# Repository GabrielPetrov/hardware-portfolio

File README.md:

# PCB Design Portfolio

A collection of PCB projects I worked on while studying at TUES (ELSYS).

These were academic projects and were primarily intended as PCB design exercises rather than finished products. They cover work in KiCad and Cadence OrCAD, from simple analog boards to larger MCU-based designs.

## Projects

### Implant
Compact BLE sensor concept based around an nRF52811 and AD5941, with impedance and temperature sensing and energy-harvesting/power circuitry.

[Project files](./Implant/)

### DogTracker
Battery-powered ESP32-C3 tracker with GNSS, microSD storage, temperature measurement and associated power-management circuitry.

[Project files](./DogTracker/)

### DS0201v1.1
My first PCB design project. I produced 2-layer and 4-layer versions in Cadence OrCAD and later remade both versions in KiCad.

[Project files](./DS0201v1.1/)

### Analog Front End
Small thermistor measurement board using op-amp signal conditioning and an external ADC.

[Project files](./AFE/)

## Other projects

Two other embedded projects I've worked on are available separately:

- **[SeeIT](https://github.com/GabrielPetrov/SeeIT)** - ESP32 and Raspberry Pi-based computer-vision project.
- **[Furchikopter](https://github.com/Nikieprogramach/Furchikopter)** - remote-controlled aircraft using Arduino Uno boards and LoRa communication.

## Tools

Most of my PCB work has been done in KiCad. I originally learned the PCB design workflow using Cadence OrCAD 10.5 (Capture CIS, Layout and PSpice A/D), and I also have experience using LTspice for circuit simulation.

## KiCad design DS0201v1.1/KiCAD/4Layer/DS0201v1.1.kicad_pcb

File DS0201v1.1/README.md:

# DS0201

DS0201 was my first PCB design project and the board I originally used to learn the PCB design workflow.

The original versions were made in Cadence OrCAD 10.5. I produced both a 2-layer and a 4-layer layout, working from the same schematic.

The board is based around an STM32F103 and includes several peripheral and analog sections, including SD card storage, USB and battery circuitry, RS-232, switching/multiplexing and analog signal-conditioning circuitry.

## Original OrCAD versions

### Schematic

[View full schematic PDF](./Cadence%20OrCAD%20v10.5/Schematic_CaptureCIS/DS0201_schematic.pdf)

### 2-layer layout

### 4-layer layout

## KiCad versions

After completing the original OrCAD layouts, I recreated the board in KiCad in both 2-layer and 4-layer form.

The KiCad versions were done fairly quickly as an exercise in transferring the same design to a different EDA rather than as a complete layout redesign. Because of that, component placement and layout optimisation were not the main focus of those versions.

The project was useful for comparing the workflow of the two EDA packages and for seeing how the same design changes when moving between two and four copper layers.

### Schematic

[View full schematic PDF](./KiCAD/Schematic.pdf)

### 2-layer layout

[View full 2-layer PCB PDF](./KiCAD/2Layer/2LayerPCB.pdf)

### 4-layer layout

[View full 4-layer PCB PDF](./KiCAD/4Layer/4LayerPCB.pdf)

## Project files

The repository also contains the original OrCAD project files and the KiCad project files for both layouts.

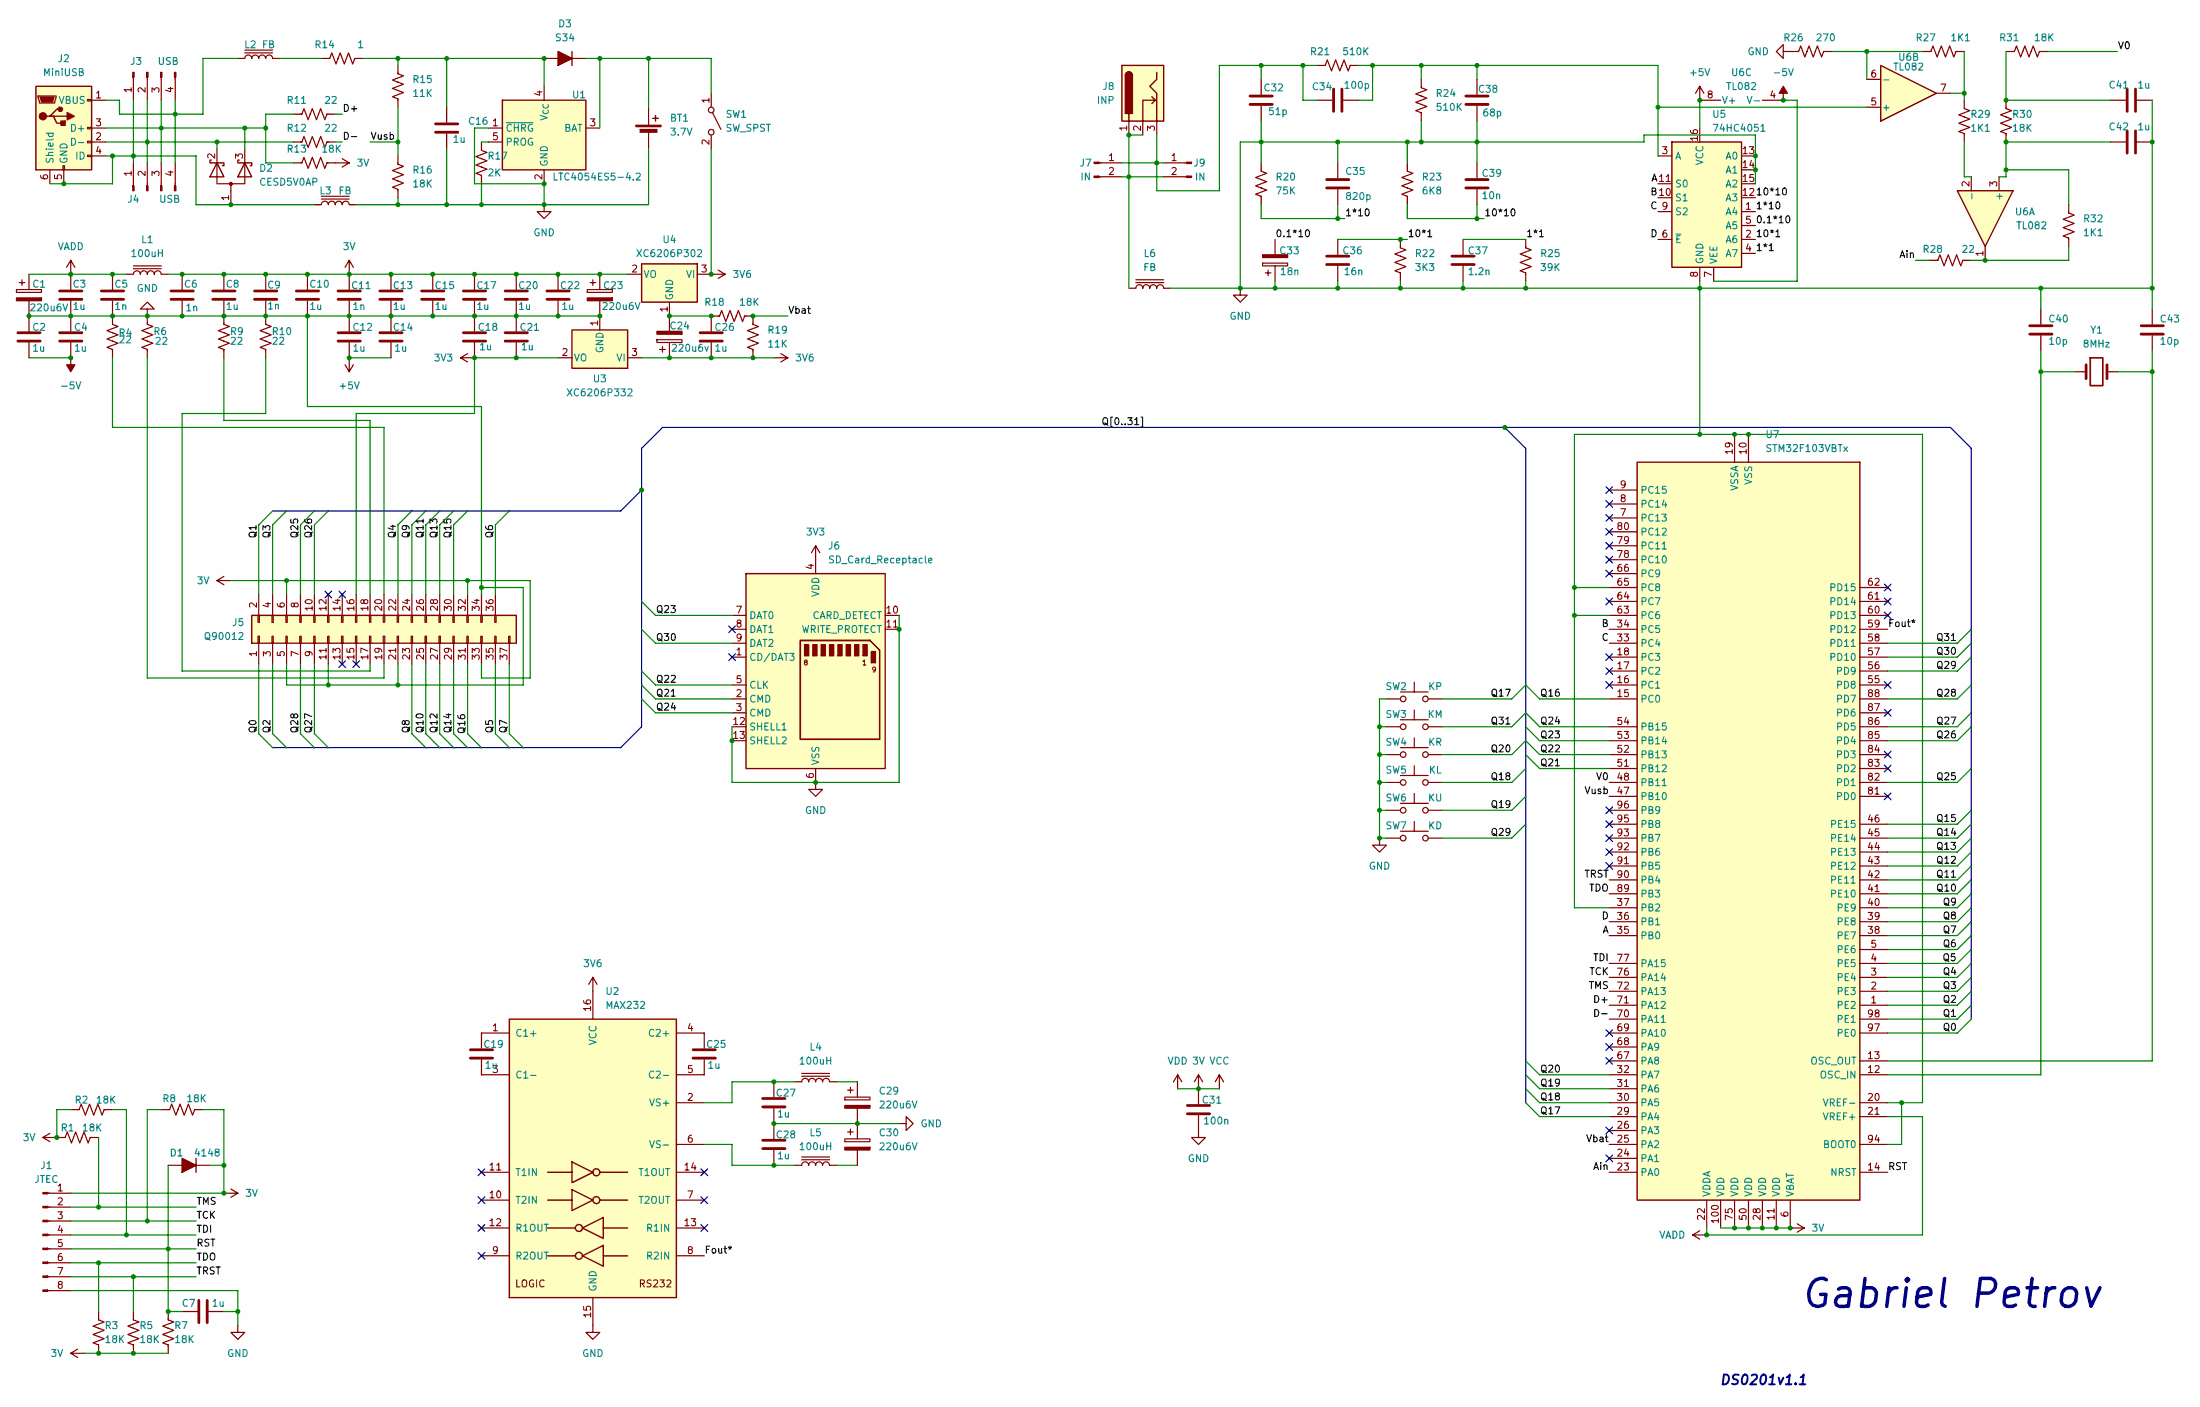
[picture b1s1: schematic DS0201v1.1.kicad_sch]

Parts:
BT1: 3.7V; JST_PH_B2B-PH-K_1x02_P2.00mm_Vertical
C1, C23, C29, C30: 220u6V; C_Radial_D6.3mm_H11.0mm_P2.50mm
C2, C3, C4, C7, C8, C10, C12, C13, C14, C15, C16, C17, C18, C19, C20, C21, C22, C25, C26, C27, C28, C41, C42: 1u; C_Disc_D3.8mm_W2.6mm_P2.50mm
C5, C6, C9, C11: 1n; C_Disc_D3.8mm_W2.6mm_P2.50mm
C24: 220u6v; C_Radial_D6.3mm_H11.0mm_P2.50mm
C31: 100n; C_Disc_D3.8mm_W2.6mm_P2.50mm
C32: 51p; C_Disc_D3.8mm_W2.6mm_P2.50mm
C33: 18n; C_Disc_D3.8mm_W2.6mm_P2.50mm
C34: 100p; C_Disc_D3.8mm_W2.6mm_P2.50mm
C35: 820p; C_Disc_D3.8mm_W2.6mm_P2.50mm
C36: 16n; C_Axial_L3.8mm_D2.6mm_P7.50mm_Horizontal
C37: 1.2n; C_Disc_D3.8mm_W2.6mm_P2.50mm
C38: 68p; C_Disc_D3.8mm_W2.6mm_P2.50mm
C39: 10n; C_Disc_D3.8mm_W2.6mm_P2.50mm
C40, C43: 10p; C_Disc_D3.8mm_W2.6mm_P2.50mm
D1: 4148; D_5W_P12.70mm_Horizontal
D2: CESD5V0AP; SOT-23
D3: S34; D_SOD-123F
J1: JTEC; Molex_Micro-Fit_3.0_43650-0815_1x08_P3.00mm_Vertical
J2: MiniUSB; USB_Micro-B_Wuerth_629105150521_CircularHoles
J3, J4: USB; Harwin_LTek-Male_04_P2.00mm_Vertical
J5: Q90012; Hirose_FH12-36S-0.5SH_1x36-1MP_P0.50mm_Horizontal
J6: SD_Card_Receptacle; CONN9_MSD-1_CUD
J7, J9: IN; Wuerth_WR-WTB_64800211622_1x02_P1.50mm_Vertical
J8: INP; MMCX_Molex_73415-0961_Horizontal_1.6mm-PCB
L1, L4, L5: 100uH; CP_Radial_D8.0mm_P3.50mm
L2, L3, L6: FB; CP_Radial_D8.0mm_P3.50mm
R1, R2, R3, R5, R7, R8, R13, R16, R18, R30, R31: 18K; R_Axial_DIN0204_L3.6mm_D1.6mm_P5.08mm_Horizontal
R4, R6, R9, R10, R11, R12, R28: 22; R_Axial_DIN0204_L3.6mm_D1.6mm_P5.08mm_Horizontal
R14: 1; R_Axial_DIN0204_L3.6mm_D1.6mm_P5.08mm_Horizontal
R15, R19: 11K; R_Axial_DIN0204_L3.6mm_D1.6mm_P5.08mm_Horizontal
R17: 2K; R_Axial_DIN0204_L3.6mm_D1.6mm_P5.08mm_Horizontal
R20: 75K; R_Axial_DIN0204_L3.6mm_D1.6mm_P5.08mm_Horizontal
R21, R24: 510K; R_Axial_DIN0204_L3.6mm_D1.6mm_P5.08mm_Horizontal
R22: 3K3; R_Axial_DIN0204_L3.6mm_D1.6mm_P5.08mm_Horizontal
R23: 6K8; R_Axial_DIN0204_L3.6mm_D1.6mm_P5.08mm_Horizontal
R25: 39K; R_Axial_DIN0204_L3.6mm_D1.6mm_P5.08mm_Horizontal
R26: 270; R_Axial_DIN0204_L3.6mm_D1.6mm_P5.08mm_Horizontal
R27, R29, R32: 1K1; R_Axial_DIN0204_L3.6mm_D1.6mm_P5.08mm_Horizontal
SW1: SW_SPST; SW_DIP_SPSTx01_Slide_9.78x4.72mm_W7.62mm_P2.54mm
SW2: KP; SW_PUSH_6mm
SW3: KM; SW_PUSH_6mm
SW4: KR; SW_PUSH_6mm
SW5: KL; SW_PUSH_6mm
SW6: KU; SW_PUSH_6mm
SW7: KD; SW_PUSH_6mm
U1: LTC4054ES5-4.2; TSOT-23-5
U2: MAX232; CERDIP-16_W7.62mm_SideBrazed
U3: XC6206P332; SOT-23-3
U4: XC6206P302; SOT-23-3
U5: 74HC4051; SOP-16_4.55x10.3mm_P1.27mm
U6: TL082; DIP-8_W7.62mm
U7: STM32F103VBTx; LQFP-100_14x14mm_P0.5mm
Y1: 8MHz; Crystal_AT310_D3.0mm_L10.0mm_Vertical

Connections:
3V: C6.1, C8.1, C9.1, C10.1, C11.1, C13.1, C15.1, C17.1, C20.1, C22.1, C23.1, C31.1, D1.1 (K), J1.1, J5.6, J5.32, J5.33, L1.2, R1.1, R2.1, R3.2, R5.2, R7.2, R8.2, R13.2, U4.2 (VO), U7.6 (VBAT), U7.11 (VDD), U7.28 (VDD), U7.50 (VDD), U7.75 (VDD), U7.100 (VDD)
3V3: C18.2, C21.2, J5.16, J6.4 (VDD), U3.2 (VO)
3V6: C24.1, C26.2, R19.2, SW1.2 (B), U2.16 (VCC), U3.3 (VI), U4.3 (VI)
+5V: C12.2, C14.2, U5.16 (VCC), U6.8 (V+)
-5V: C2.2, C4.2, U5.7 (VEE), U6.4 (V-)
/0.1*10: C33.2, U5.5 (A5)
/1*1: C37.1, R25.1, U5.4 (A7)
/1*10: C35.2, R20.2, U5.1 (A4)
/10*1: C36.1, R22.1, U5.2 (A6)
/10*10: C39.2, R23.2, U5.12 (A3)
/A: U5.11 (S0), U7.35 (PB0)
/Ain: R28.1, U7.23 (PA0)
/B: U5.10 (S1), U7.34 (PC5)
/C: U5.9 (S2), U7.33 (PC4)
/D: U5.6 (~E), U7.36 (PB1)
/D+: R11.2, U7.71 (PA12)
/D-: R12.2, U7.70 (PA11)
/Fout*: U2.8 (R2IN), U7.59 (PD12)
/Q0: J5.1, U7.97 (PE0)
/Q1: J5.2, U7.98 (PE1)
/Q2: J5.3, U7.1 (PE2)
/Q3: J5.4, U7.2 (PE3)
/Q4: J5.22, U7.3 (PE4)
/Q5: J5.35, U7.4 (PE5)
/Q6: J5.36, U7.5 (PE6)
/Q7: J5.37, U7.38 (PE7)
/Q8: J5.23, U7.39 (PE8)
/Q9: J5.24, U7.40 (PE9)
/Q10: J5.25, U7.41 (PE10)
/Q11: J5.26, U7.42 (PE11)
/Q12: J5.27, U7.43 (PE12)
/Q13: J5.28, U7.44 (PE13)
/Q14: J5.29, U7.45 (PE14)
/Q15: J5.30, U7.46 (PE15)
/Q16: J5.31, U7.15 (PC0)
/Q17: SW2.2, U7.29 (PA4)
/Q18: SW5.2, U7.30 (PA5)
/Q19: SW6.2, U7.31 (PA6)
/Q20: SW4.2, U7.32 (PA7)
/Q21: J6.2 (CMD), U7.51 (PB12)
/Q22: J6.5 (CLK), U7.52 (PB13)
/Q23: J6.7 (DAT0), U7.53 (PB14)
/Q24: J6.3 (CMD), U7.54 (PB15)
/Q25: J5.8, U7.82 (PD1)
/Q26: J5.10, U7.85 (PD4)
/Q27: J5.9, U7.86 (PD5)
/Q28: J5.7, U7.88 (PD7)
/Q29: SW7.2, U7.56 (PD9)
/Q30: J6.9 (DAT2), U7.57 (PD10)
/Q31: SW3.2, U7.58 (PD11)
/RST: C7.1, D1.2 (A), J1.5, R7.1, U7.14 (NRST)
/TCK: J1.3, R8.1, U7.76 (PA14)
/TDI: J1.4, R2.2, U7.77 (PA15)
/TDO: J1.6, R3.1, U7.89 (PB3)
/TMS: J1.2, R1.2, U7.72 (PA13)
/TRST: J1.7, R5.1, U7.90 (PB4)
/V0: R31.2, U7.48 (PB11)
/Vbat: R18.2, R19.1, U7.25 (PA2)
/Vusb: R15.2, R16.1, U7.47 (PB10)
GND: BT1.2 (-), C1.2, C2.1, C3.2, C4.1, C5.2, C6.2, C7.2, C8.2, C9.2, C10.2, C11.2, C12.1, C13.2, C14.1, C15.2, C16.2, C17.2, C18.1, C20.2, C21.1, C22.2, C23.2, C27.2, C28.1, C29.2, C30.1, C31.2, C32.1, C33.1, C35.1, C36.2, C37.2, C38.2, C39.1, C40.1, C41.2, C42.2, C43.1, J1.8, J5.5, J5.11, J5.21, J5.34, J6.6 (VSS), J6.10 (CARD_DETECT), J6.11 (WRITE_PROTECT), J6.12 (SHELL1), J6.13 (SHELL2), L3.2, L6.2, R4.1, R6.1, R9.1, R10.1, R16.2, R17.2, R20.1, R22.2, R23.1, R24.2, R25.2, R26.1, SW2.1, SW3.1, SW4.1, SW5.1, SW6.1, SW7.1, U1.1 (~CHRG), U1.2 (GND), U2.15 (GND), U3.1 (GND), U5.8 (GND), U5.13 (A0), U5.14 (A1), U5.15 (A2), U7.10 (VSS), U7.19 (VSSA), U7.20 (VREF-), U7.27 (VSS), U7.37 (PB2), U7.49 (VSS), U7.63 (PC6), U7.65 (PC8), U7.74 (VSS), U7.94 (BOOT0), U7.99 (VSS)
unnamed: BT1.1 (+), D3.1 (K), SW1.1 (A), U1.3 (BAT)
unnamed: C29.1, L4.2
unnamed: C30.2, L5.2
unnamed: C41.1, R30.1, R31.1
unnamed: D2.1 (A), J2.4 (ID), J2.5 (GND), J2.6 (Shield), J3.1, J4.1, L3.1
unnamed: C16.1, D3.2 (A), R14.2, R15.1, U1.4 (V_{CC})
unnamed: D2.3 (K), J2.3 (D+), J3.3, J4.3, R11.1, R13.1
unnamed: D2.2 (K), J2.2 (D-), J3.2, J4.2, R12.1
unnamed: J2.1 (VBUS), J3.4, J4.4, L2.1
unnamed: J5.17, R10.2
unnamed: J5.18, R9.2
unnamed: J5.19, R6.2
unnamed: J5.20, R4.2
unnamed: C32.2, C34.2, J7.1, J8.3, J9.1, R21.1
unnamed: J7.2, J8.1, J8.2, J9.2, L6.1
unnamed: L2.2, R14.1
unnamed: R27.2, R29.1, U6.7
unnamed: R28.2, R32.2, U6.1
unnamed: R17.1, U1.5 (PROG)
unnamed: C19.1, U2.1 (C1+)
unnamed: C19.2, U2.3 (C1-)
unnamed: C25.1, U2.4 (C2+)
unnamed: C25.2, U2.5 (C2-)
unnamed: C27.1, L4.1, U2.2 (VS+)
unnamed: C28.2, L5.1, U2.6 (VS-)
unnamed: C24.2, C26.1, R18.1, U4.1 (GND)
unnamed: C34.1, C38.1, R21.2, R24.1, U5.3 (A), U6.5 (+)
unnamed: C42.1, R30.2, R32.1, U6.3 (+)
unnamed: R29.2, U6.2 (-)
unnamed: R26.2, R27.1, U6.6 (-)
unnamed: C40.2, U7.12 (OSC_IN), Y1.1
unnamed: C43.2, U7.13 (OSC_OUT), Y1.2
VADD: C1.1, C3.1, C5.1, L1.1, U7.21 (VREF+), U7.22 (VDDA)

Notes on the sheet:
Gabriel Petrov
DS0201v1.1

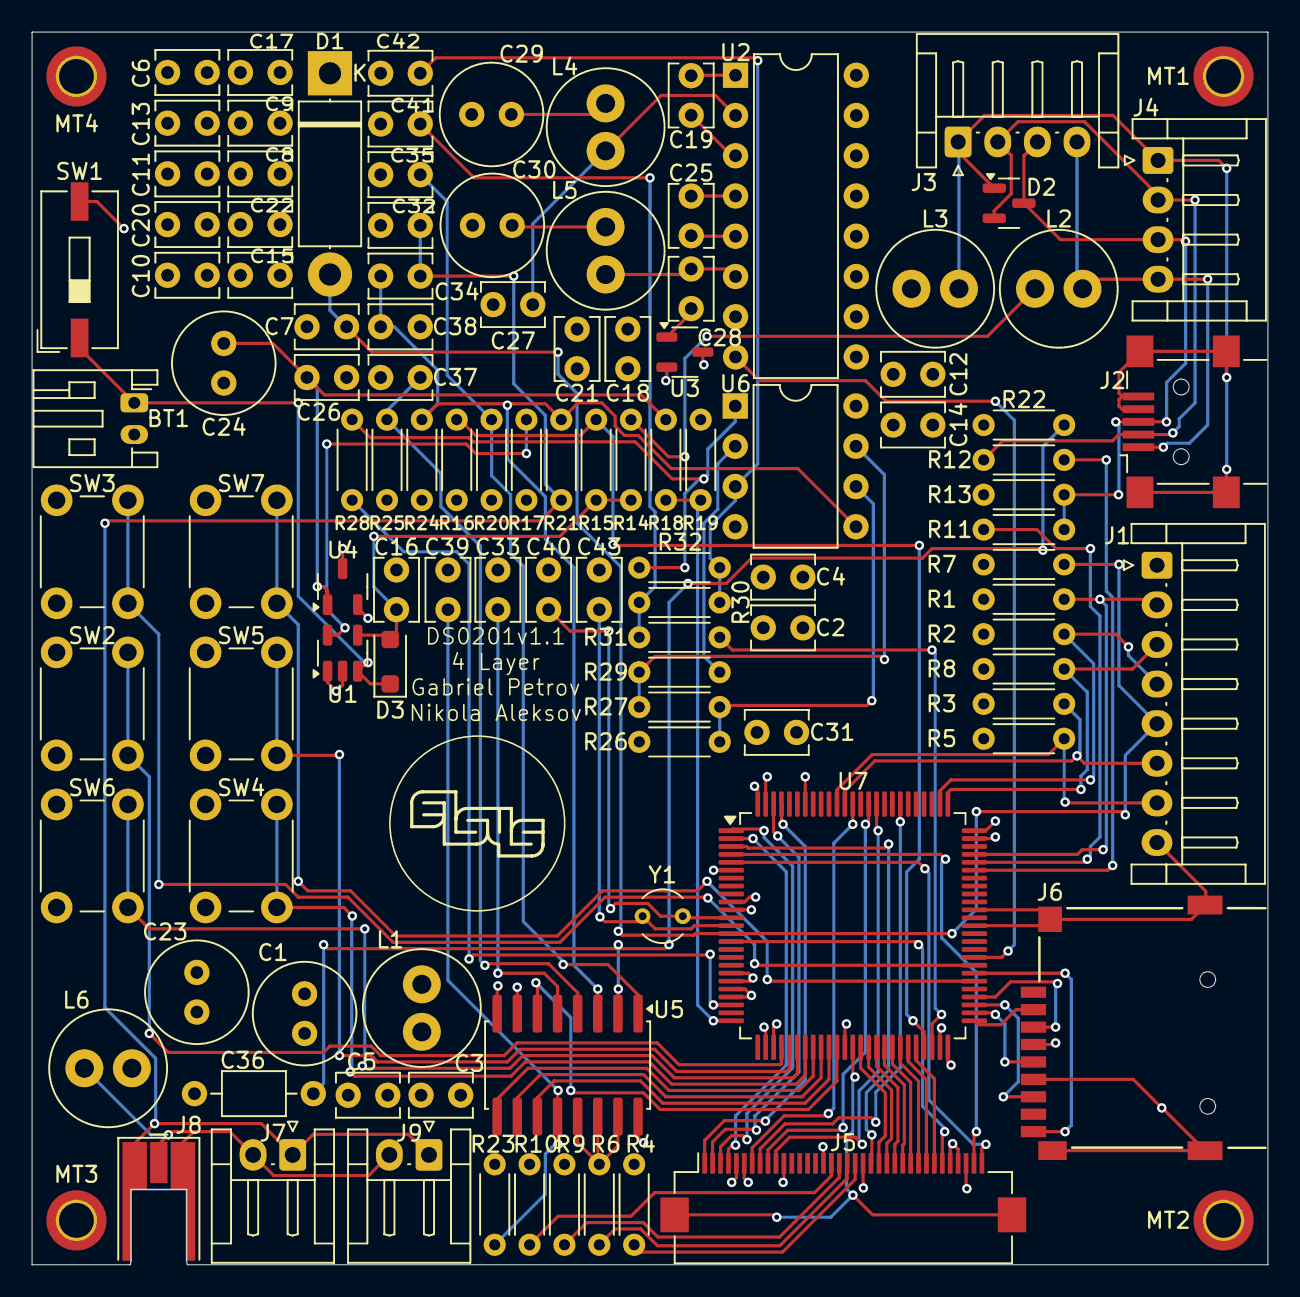
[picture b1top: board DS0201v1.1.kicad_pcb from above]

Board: 4 copper layers, 78.0 x 77.8 mm, 113 parts (0 on the bottom side), 93 nets.

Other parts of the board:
MT1, MT2, MT3, MT4: MountingHole_2.2mm_M2_DIN965_Pad_TopBottom

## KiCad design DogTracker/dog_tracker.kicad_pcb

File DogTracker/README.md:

# DogTracker

DogTracker was a school project for a small battery-powered tracking device.

The board is based around an ESP32-C3 and an L80-R GNSS module. It also includes microSD storage, temperature measurement, a serial EEPROM, and the supporting battery charging and power circuitry.

The schematic and PCB were designed in KiCad.

## Main parts

- ESP32-C3-WROOM-02
- L80-R GNSS module
- MicroSD card
- Li-ion battery and USB-C charging
- TPS63031 buck-boost converter
- Thermistor measurement circuitry
- External ADC
- Serial EEPROM

## Design

The board was designed to fit inside a roughly 50 mm circular outline. The project involved fitting the MCU, GNSS module, storage, sensors and power circuitry onto the same board while keeping the different sections reasonably separated.

## Schematic

[View full schematic PDF](./DogTrackSchema.pdf)

## PCB

[View full PCB PDF](./dog_tracker-User_2.pdf)

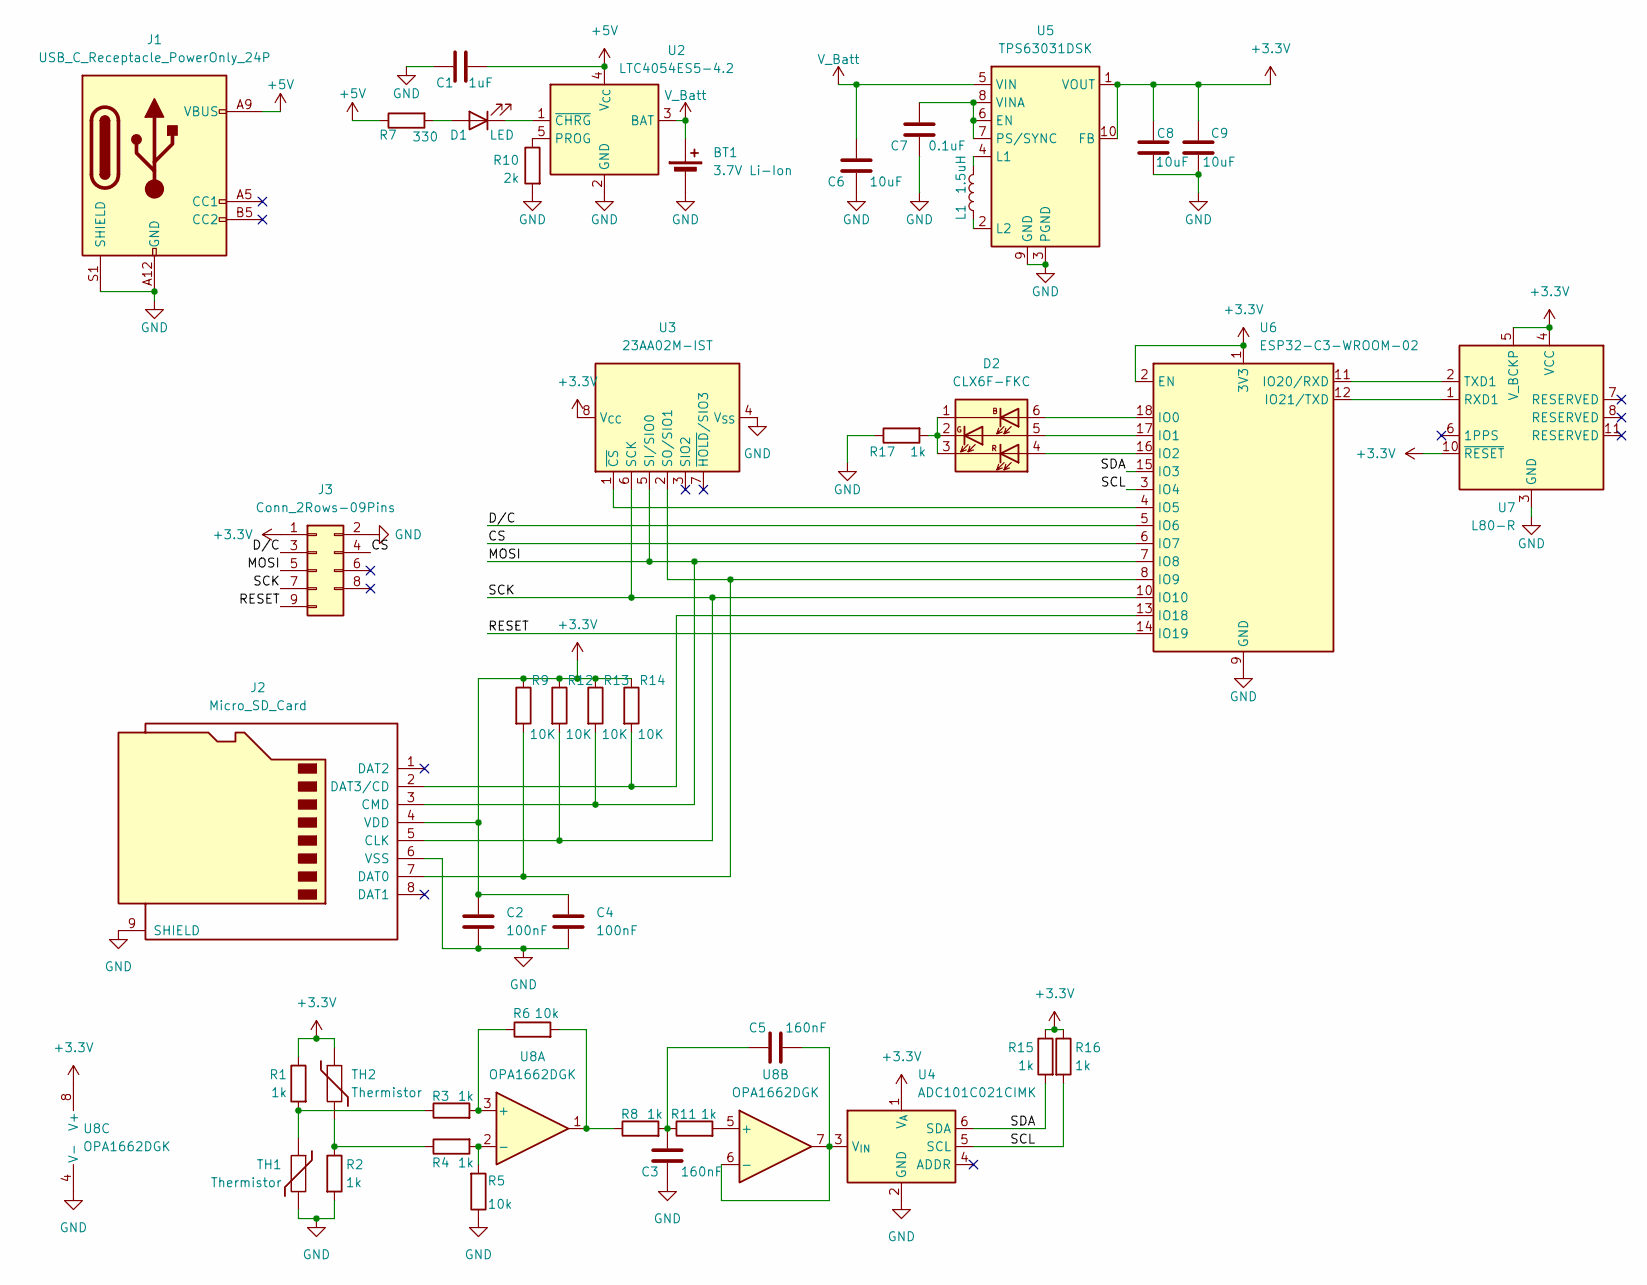
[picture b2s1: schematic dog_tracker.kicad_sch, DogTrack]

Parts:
BT1: 3.7V Li-Ion; vapcell_inr_26350_footprint
C1: 1uF; R_0201_0603Metric
C2, C4: 100nF; R_0201_0603Metric
C3, C5: 160nF; R_0201_0603Metric
C6, C8, C9: 10uF; C_0201_0603Metric
C7: 0.1uF; C_0201_0603Metric
D1: LED; D_0201_0603Metric
D2: CLX6F-FKC; LED_RGB_PLCC-6
J1: USB_C_Receptacle_PowerOnly_24P; USB_C_Receptacle_Amphenol_124019772112A
J2: Micro_SD_Card; microSD_HC_Hirose_DM3BT-DSF-PEJS
J3: Conn_2Rows-09Pins; Hirose_DF13C_CL535-0410-4-51_1x10-1MP_P1.25mm_Vertical
L1: 1.5uH; L_0201_0603Metric
R1, R2, R3, R4, R8, R11, R15, R16, R17: 1k; R_0201_0603Metric
R5, R6: 10k; R_0201_0603Metric
R7: 330; R_0201_0603Metric
R9, R12, R13, R14: 10K; R_0201_0603Metric
R10: 2k; R_0201_0603Metric
TH1, TH2: Thermistor; R_0201_0603Metric
U2: LTC4054ES5-4.2; TSOT-23-5
U3: 23AA02M-IST; TSSOP-8_4.4x3mm_P0.65mm
U4: ADC101C021CIMK; SOT-23-6
U5: TPS63031DSK; WSON-10-1EP_2.5x2.5mm_P0.5mm_EP1.2x2mm
U6: ESP32-C3-WROOM-02
U7: L80-R; Quectel_L80-R
U8: OPA1662DGK; VSSOP-8_3x3mm_P0.65mm

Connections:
+3.3V: C2.1, C4.1, C8.2, C9.2, J2.4 (VDD), J3.1, R1.1, R9.1, R12.1, R13.1, R14.1, R15.1, R16.1, TH2.1, U3.8 (V_{CC}), U4.1 (V_{A}), U5.1 (VOUT), U5.10 (FB), U6.1 (3V3), U6.2 (EN), U7.4 (VCC), U7.5 (V_BCKP), U7.10 (~RESET), U8.8 (V+)
+5V: C1.1, J1.A4 (VBUS), J1.A9 (VBUS), J1.B4 (VBUS), J1.B9 (VBUS), R7.1, U2.4 (V_{CC})
/CS: J3.4, U6.6 (IO7)
/D/C: J3.3, U6.5 (IO6)
/MOSI: J2.3 (CMD), J3.5, R13.2, U3.5 (SI/SIO0), U6.7 (IO8)
/RESET: J3.9, U6.14 (IO19)
/SCK: J2.5 (CLK), J3.7, R12.2, U3.6 (SCK), U6.10 (IO10)
/SCL: R16.2, U4.5 (SCL), U6.3 (IO4)
/SDA: R15.2, U4.6 (SDA), U6.15 (IO3)
GND: BT1.2 (-), C1.2, C2.2, C3.2, C4.2, C6.1, C7.1, C8.1, C9.1, J1.A1 (GND), J1.A12 (GND), J1.B1 (GND), J1.B12 (GND), J1.S1 (SHIELD), J2.6 (VSS), J2.9 (SHIELD), J3.2, R2.2, R5.1, R10.2, R17.1, TH1.2, U2.2 (GND), U3.4 (V_{SS}), U4.2 (GND), U5.3 (PGND), U5.9 (GND), U5.11 (PGND), U6.9 (GND), U6.19 (GND), U7.3 (GND), U7.12 (GND), U8.4 (V-)
unnamed: C3.1, C5.2, R8.2, R11.1
unnamed: D1.2 (A), R7.2
unnamed: D1.1 (K), U2.1 (~CHRG)
unnamed: D2.6 (AB), U6.18 (IO0)
unnamed: D2.5 (AG), U6.17 (IO1)
unnamed: D2.4 (AR), U6.16 (IO2)
unnamed: D2.1 (KB), D2.2 (KG), D2.3 (KR), R17.2
unnamed: J2.7 (DAT0), R9.2, U3.2 (SO/SIO1), U6.8 (IO9)
unnamed: J2.2 (DAT3/CD), R14.2, U6.13 (IO18)
unnamed: R1.2, R3.1, TH1.1
unnamed: R2.1, R4.1, TH2.2
unnamed: R6.2, R8.1, U8.1
unnamed: R10.1, U2.5 (PROG)
unnamed: U3.1 (~CS), U6.4 (IO5)
unnamed: C5.1, U4.3 (V_{IN}), U8.6 (-), U8.7
unnamed: C7.2, U5.6 (EN), U5.7 (PS/SYNC), U5.8 (VINA)
unnamed: L1.2, U5.4 (L1)
unnamed: L1.1, U5.2 (L2)
unnamed: U6.11 (IO20/RXD), U7.2 (TXD1)
unnamed: U6.12 (IO21/TXD), U7.1 (RXD1)
unnamed: R3.2, R6.1, U8.3 (+)
unnamed: R4.2, R5.2, U8.2 (-)
unnamed: R11.2, U8.5 (+)
V_Batt: BT1.1 (+), C6.2, U2.3 (BAT), U5.5 (VIN)

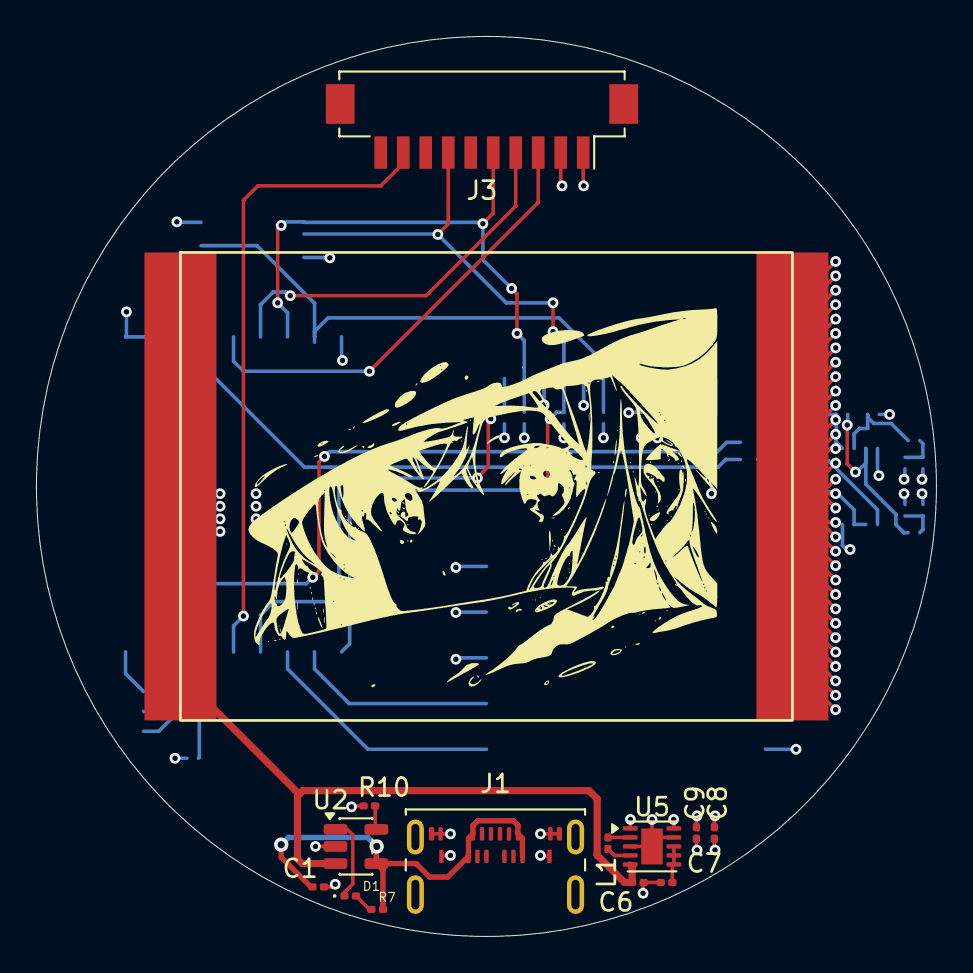
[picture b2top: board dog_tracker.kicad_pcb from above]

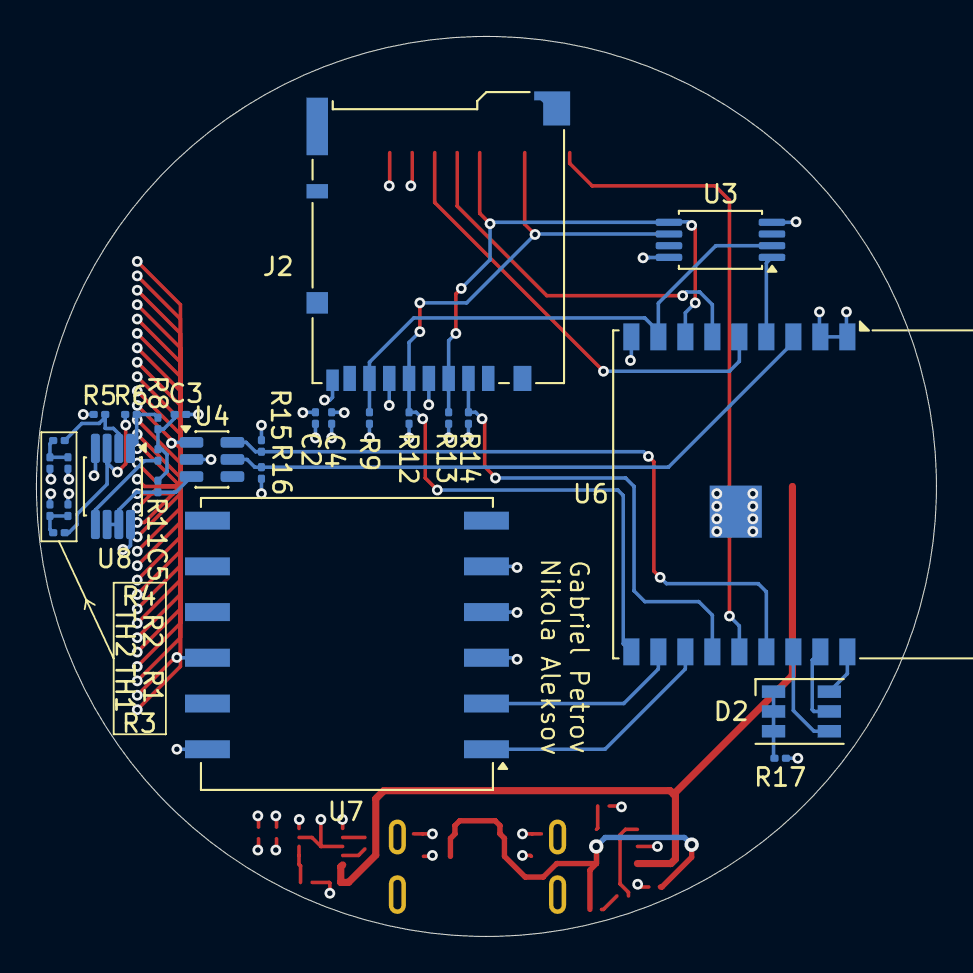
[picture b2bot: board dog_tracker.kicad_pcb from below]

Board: 4 copper layers, 50.0 x 50.0 mm, 42 parts (28 on the bottom side), 34 nets.

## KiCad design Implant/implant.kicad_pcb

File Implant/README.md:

# Implant-Inspired Wireless Sensor

A school PCB project for a compact wireless sensor intended to measure impedance and temperature.

The design is based around an nRF52811 BLE SoC and an AD5941 analog front end for impedance measurement. It also includes temperature sensing and power circuitry based around energy harvesting and supercapacitor storage.

## Main parts

- nRF52811 BLE SoC
- AD5941 impedance-measurement AFE
- LTC3588-1 energy-harvesting IC
- CAP-XX supercapacitor
- NTC temperature sensor
- 2.4 GHz antenna and matching components

The project involved combining digital, analog, RF and power sections on a single PCB and working through the component, footprint and layout requirements of each.

It was an implant-inspired academic design concept.

## Schematic

[View full schematic PDF](./Implant_schema.pdf)

## PCB

[View full PCB PDF](./implant.pdf)

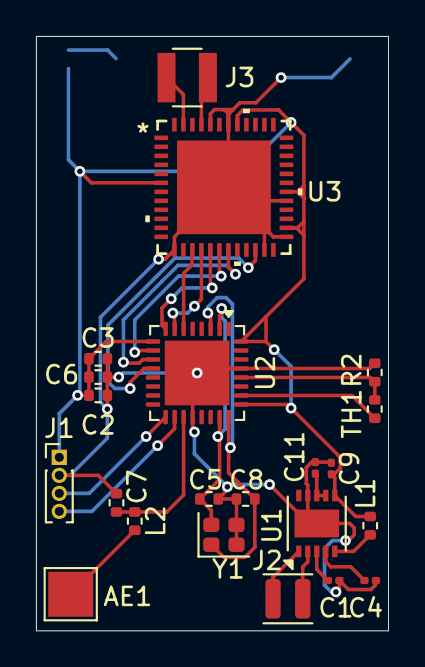
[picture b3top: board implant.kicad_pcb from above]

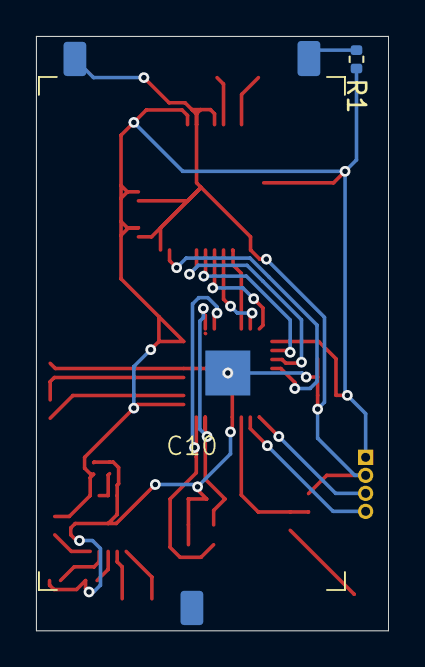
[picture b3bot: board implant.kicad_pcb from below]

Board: 2 copper layers, 19.6 x 33.0 mm, 24 parts (2 on the bottom side), 25 nets.

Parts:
AE1: Antenna; TestPoint_Pad_2.5x2.5mm
C1: 1uF; C_0201_0603Metric
C2, C3, C6: 100nF; R_0402_1005Metric
C4: 10uF; C_0201_0603Metric
C5, C8: 22p; R_0402_1005Metric
C7: 0.8p; R_0402_1005Metric
C9: 47uF; C_0201_0603Metric
C10: supercap; CAP-XX HW203F
C11: 4.7uF; C_0201_0603Metric
J1: debug; PinHeader_1x04_P1.00mm_Vertical
J2: piezo; L_APV_ANR252010
J3: electrode; L_Abracon_ASPI-3012S
L1: 10uH; R_0402_1005Metric
L2: 3.9n; R_0402_1005Metric
R1: 1; R_0402_1005Metric
R2: 100k; R_0402_1005Metric
TH1: Thermistor_NTC; R_0402_1005Metric
U1: LTC3588IDD-1-PBF; DFN-10-1EP_3x3mm_P0.5mm_EP1.55x2.48mm
U2: nRF52811-QCxx; QFN-32-1EP_5x5mm_P0.5mm_EP3.6x3.6mm_ThermalVias
U3: AD5941BCPZ-RL7; CP-48-4_ADI
Y1: Crystal_GND23; Crystal_SMD_2016-4Pin_2.0x1.6mm

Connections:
+3.3V: C2.1, C3.1, C6.1, C9.1, J1.1, L1.2, R1.1, U1.6 (VOUT), U2.9 (VDD), U2.25 (VDD), U2.32 (VDD), U3.6 (DVDD), U3.26 (IOVDD), U3.30 (AVDD), U3.41 (AVDD)
/INT: U2.11 (P0.14), U3.19 (GPIO0)
/RESET: U2.12 (P0.15), U3.22 (*RESET)
/SPI_CS: U2.6 (P0.06), U3.15 (*CS)
/SPI_MISO: U2.10 (P0.12), U3.18 (MISO)
/SPI_MOSI: U2.8 (P0.10), U3.17 (MOSI)
/SPI_SCLK: U2.7 (P0.09), U3.16 (SCLK)
/XL1: C5.1, U2.2 (XL1/P0.00), U2.23 (XC1), Y1.4
/XL2: C8.1, U2.3 (XL2/P0.01), U2.24 (XC2), Y1.1
GND: C1.2, C2.2, C3.2, C4.2, C5.2, C6.2, C7.1, C8.2, C9.2, C10.2, C11.2, J1.2, R2.2, U1.9 (D0), U1.11 (EPAD), U2.20 (VSS), U2.29 (VSS), U2.33 (VSS), U3.13 (DGND), U3.23 (DGND), U3.25 (DGND), U3.29 (AGND), U3.42 (AGND), U3.44 (AGND_REF), U3.49 (GND), Y1.2, Y1.3
unnamed: AE1.1 (A), L2.2
unnamed: C10.1, R1.2
unnamed: J1.3, U2.17 (SWDCLK)
unnamed: J1.4, U2.18 (SWDIO)
unnamed: J2.1, U1.1 (PZ1)
unnamed: J2.2, U1.2 (PZ2)
unnamed: J3.1, U3.45 (SE0)
unnamed: J3.2, U3.47 (CE0)
unnamed: C1.1, U1.3 (CAP)
unnamed: C11.1, U1.7 (VIN2), U1.8 (D1)
unnamed: L1.1, U1.5 (SW)
unnamed: C4.1, U1.4 (VIN)
unnamed: R2.1, TH1.2, U2.28 (AIN6/P0.30)
unnamed: C7.2, L2.1, U2.19 (ANT)
unnamed: TH1.1, U2.26 (P0.25)

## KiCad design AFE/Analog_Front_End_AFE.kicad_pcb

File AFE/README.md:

# Analog Front End

A small analog front-end board made as a school PCB exercise.

The circuit takes inputs from two thermistors, conditions the signals using a dual op-amp stage and sends the resulting measurement to an ADC with an I²C interface.

The board was designed in KiCad and measures approximately 17 × 17 mm.

## Main parts

- Two thermistors
- LMC6082 dual op-amp
- ADC101C021 ADC
- RC filtering
- I²C interface

The project was mainly an exercise in laying out a small mixed-signal board and working with analog signal-conditioning circuitry.

## Schematic

[View full schematic PDF](./Schematic_Gabriel_P_Nikola_A.pdf)

## PCB

[View full PCB PDF](./PCB_Gabriel_P_Nikola_A.pdf)

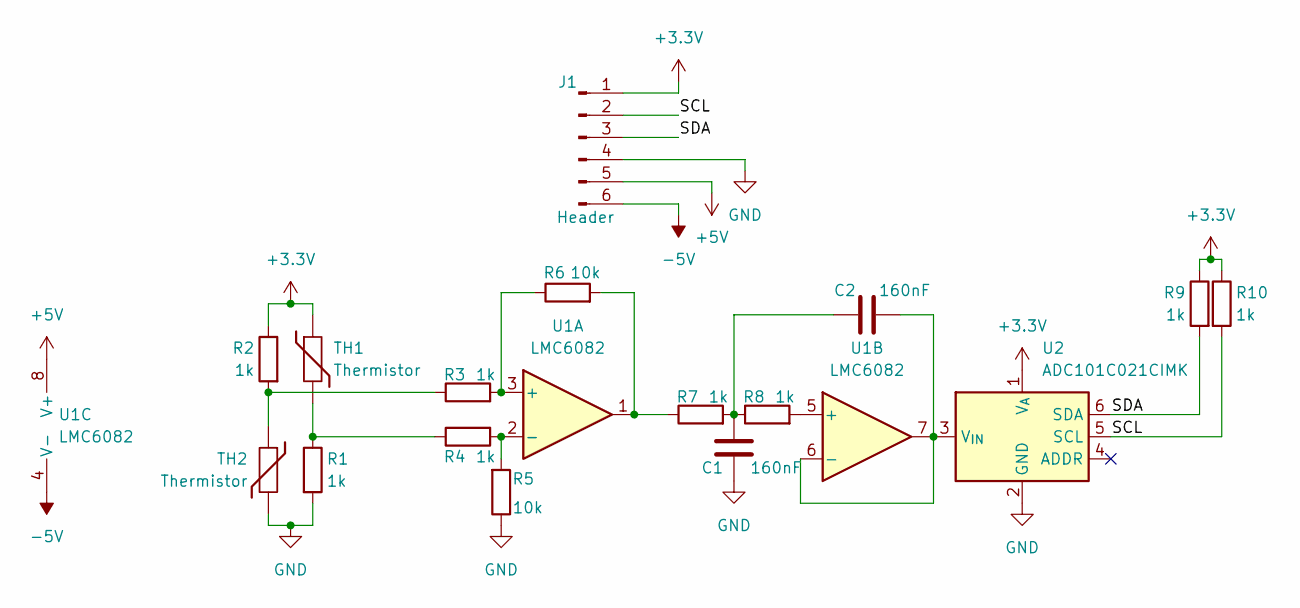
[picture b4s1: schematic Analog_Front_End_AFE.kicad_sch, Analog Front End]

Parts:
C1, C2: 160nF; R_0201_0603Metric
J1: Header; PinHeader_1x06_P2.54mm_Vertical
R1, R2, R3, R4, R7, R8, R9, R10: 1k; R_0201_0603Metric
R5, R6: 10k; R_0201_0603Metric
TH1, TH2: Thermistor; R_0201_0603Metric
U1: LMC6082; SMDIP-8_W7.62mm
U2: ADC101C021CIMK; SOT-23-6

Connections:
+3.3V: J1.1, R2.1, R9.1, R10.1, TH1.1, U2.1 (V_{A})
+5V: J1.5, U1.8 (V+)
-5V: J1.6, U1.4 (V-)
/SCL: J1.2, R10.2, U2.5 (SCL)
/SDA: J1.3, R9.2, U2.6 (SDA)
GND: C1.2, J1.4, R1.2, R5.1, TH2.2, U2.2 (GND)
unnamed: C1.1, C2.2, R7.2, R8.1
unnamed: R1.1, R4.1, TH1.2
unnamed: R2.2, R3.1, TH2.1
unnamed: R6.2, R7.1, U1.1
unnamed: R3.2, R6.1, U1.3 (+)
unnamed: R4.2, R5.2, U1.2 (-)
unnamed: R8.2, U1.5 (+)
unnamed: C2.1, U1.6 (-), U1.7, U2.3 (V_{IN})

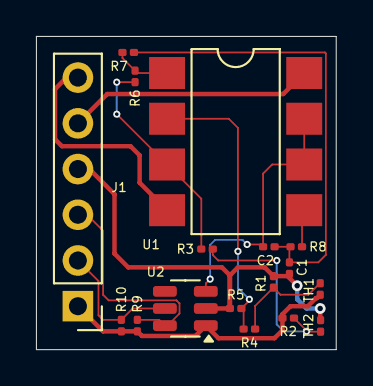
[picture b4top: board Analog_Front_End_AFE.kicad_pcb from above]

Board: 2 copper layers, 16.7 x 17.4 mm, 17 parts (0 on the bottom side), 14 nets.
